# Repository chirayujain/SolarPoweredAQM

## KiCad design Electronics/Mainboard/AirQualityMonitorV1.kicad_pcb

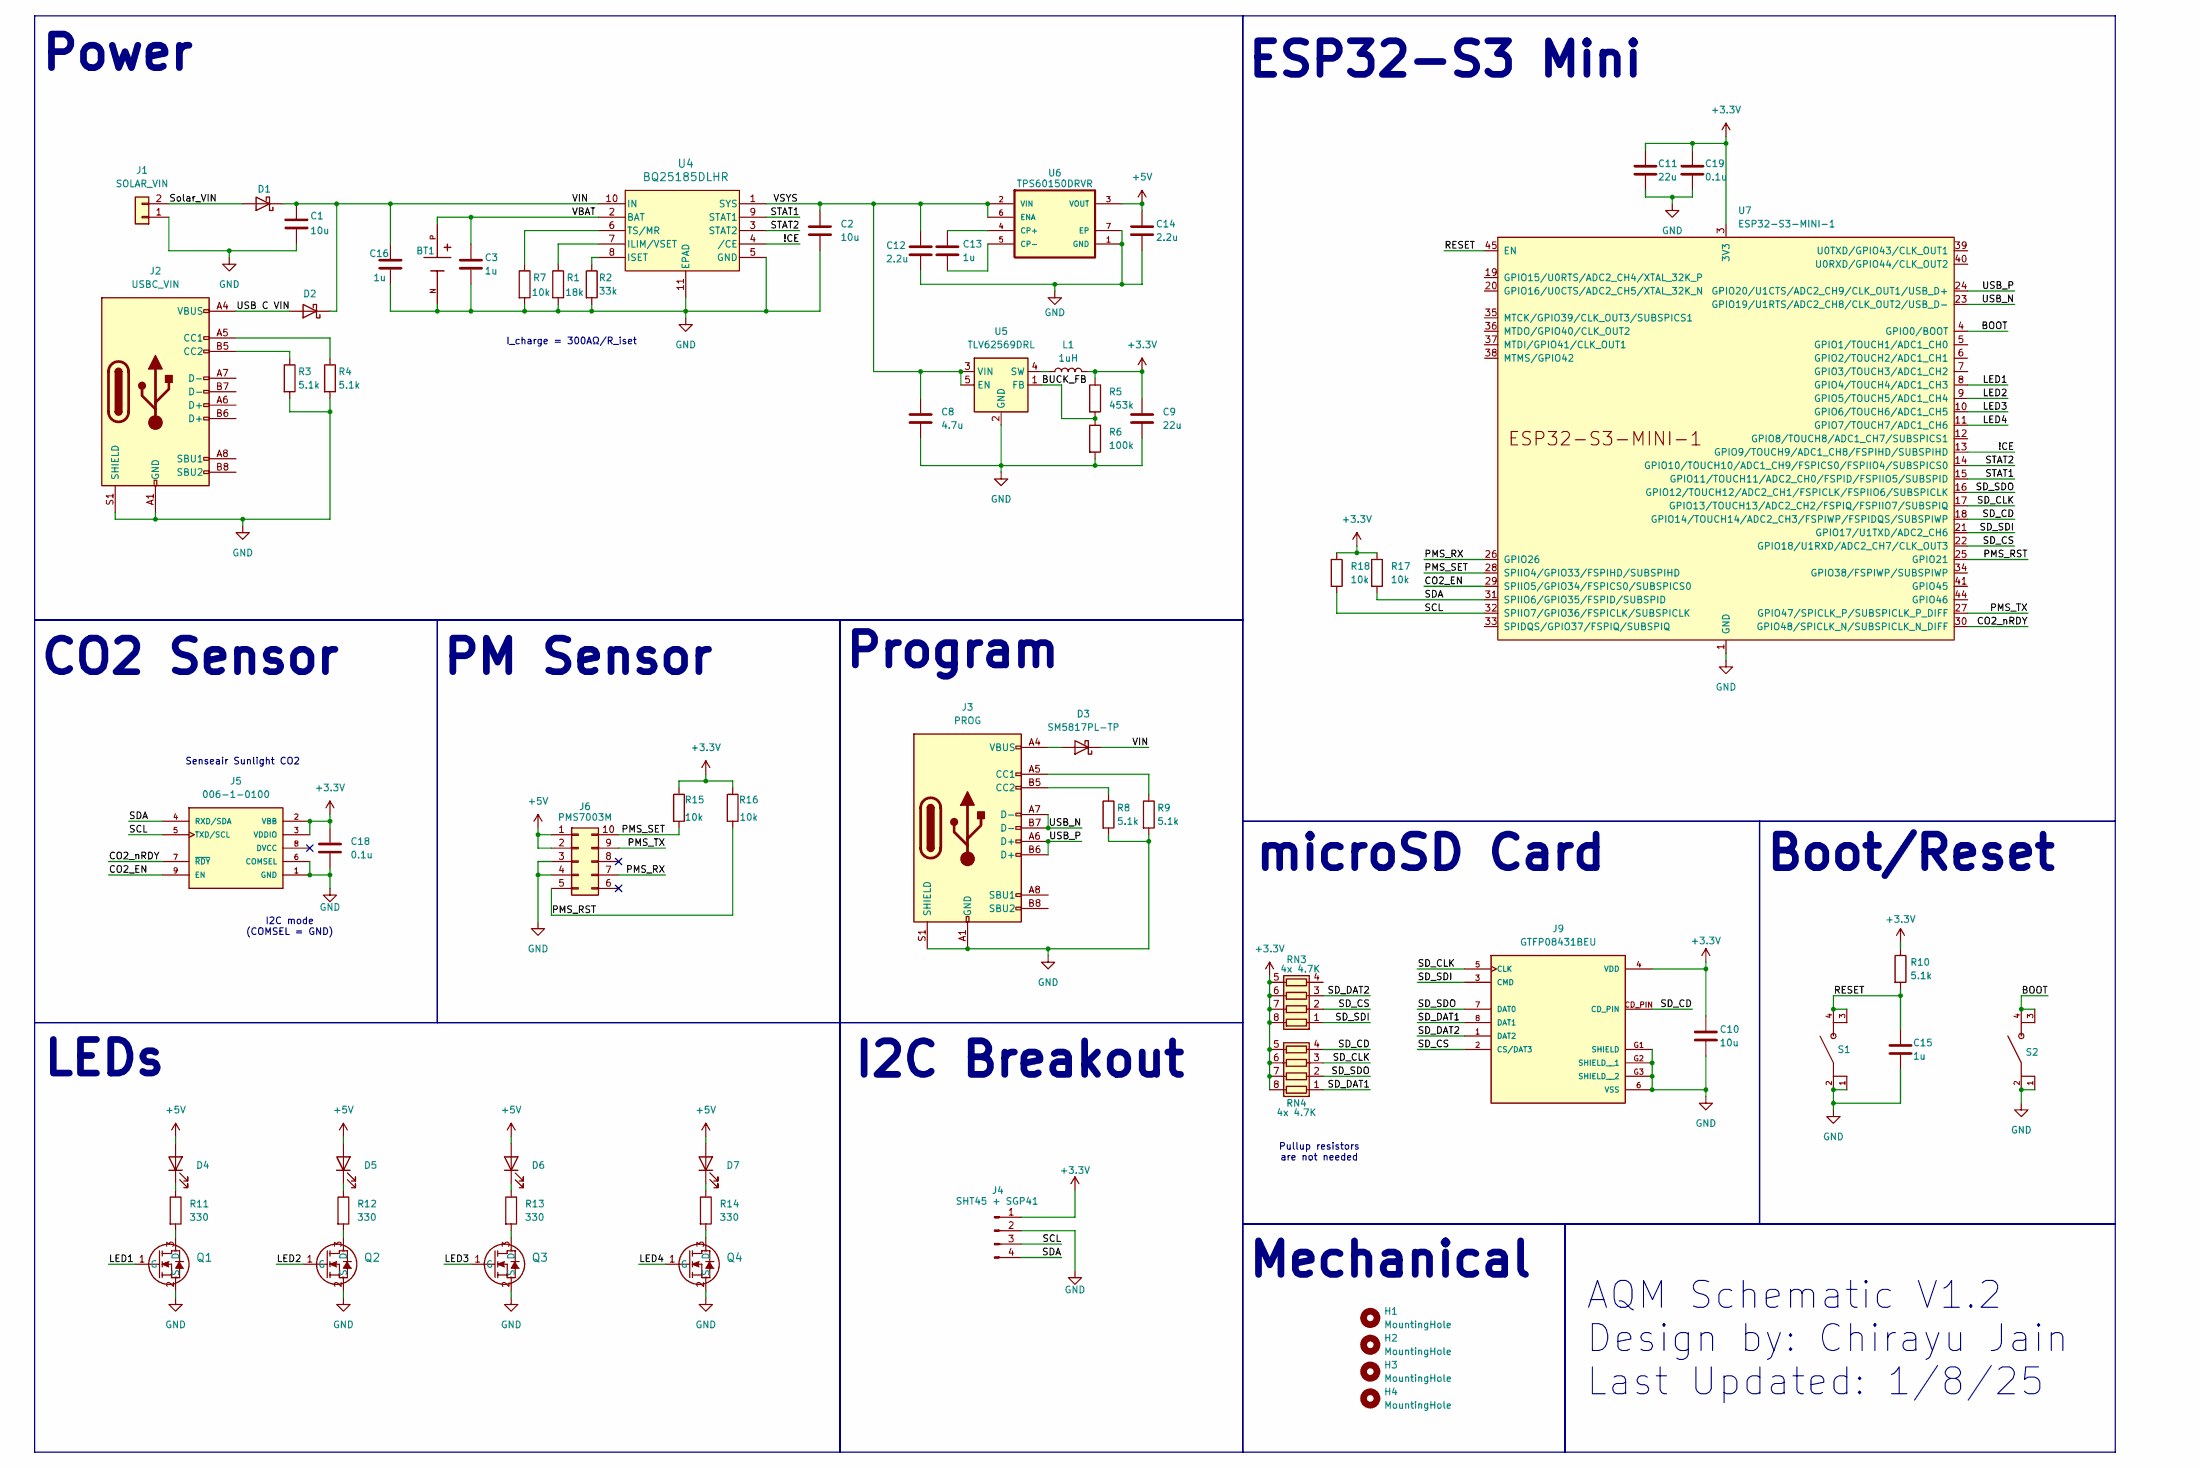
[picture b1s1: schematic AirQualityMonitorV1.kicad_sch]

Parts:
BT1: 1043; 1043_BAT_1043; PARTREV J
C1, C2, C10: 10u; C_0603_1608Metric
C3, C13, C15, C16: 1u; C_0603_1608Metric
C8: 4.7u; C_0603_1608Metric
C9, C11: 22u; C_0603_1608Metric
C12, C14: 2.2u; C_0603_1608Metric
C18, C19: 0.1u; C_0603_1608Metric
D1, D2, D3: SM5817PL-TP; D_SOD-123F
D4, D5, D6, D7: LED; LED_Luminus_MP-3030-1100_3.0x3.0mm
H1, H2, H3, H4: MountingHole; MountingHole_3.2mm_M3
J1: SOLAR_VIN; PinHeader_1x02_P2.54mm_Vertical
J2: USBC_VIN; USB_C_Receptacle_GCT_USB4105-xx-A_16P_TopMnt_Horizontal
J3: PROG; USB_C_Receptacle_GCT_USB4105-xx-A_16P_TopMnt_Horizontal
J4: SHT45 + SGP41; PinHeader_1x04_P2.54mm_Vertical
J5: 006-1-0100; 006-0-0002_XDCR_006-0-0002; PARTREV 1.00.000
J6: PMS7003M; PinSocket_2x05_P1.27mm_Vertical
J9: GTFP08431BEU; GTFP08431BEU_AMPHENOL_GTFP08431BEU; PARTREV F
L1: 1uH; L_Coilcraft_XxL4020
Q1, Q2, Q3, Q4: AO3422; SOT23_AOS
R1: 18k; R_0603_1608Metric
R2: 33k; R_0603_1608Metric
R3, R4, R8, R9, R10: 5.1k; R_0603_1608Metric
R5: 453k; R_0603_1608Metric
R6: 100k; R_0603_1608Metric
R7, R15, R16, R17, R18: 10k; R_0603_1608Metric
R11, R12, R13, R14: 330; R_0603_1608Metric
RN3, RN4: 4x 4.7K; R_Array_Convex_4x1206
S1, S2: PTS815_SJG
U4: BQ25185DLHR; WSON10_DLH_TEX
U5: TLV62569DRL; SOT-563
U6: TPS60150DRVR; TPS60150DRVR_SON65P200X200X80-7N
U7: ESP32-S3-MINI-1

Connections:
+3.3V: C9.1, C10.1, C11.1, C18.1, C19.1, J4.1, J5.2 (VBB), J5.3 (VDDIO), J9.4 (VDD), L1.2, R5.1, R10.1, R15.1, R16.1, R17.1, R18.1, RN3.5 (R4.2), RN3.6 (R3.2), RN3.7 (R2.2), RN3.8 (R1.2), RN4.5 (R4.2), RN4.6 (R3.2), RN4.7 (R2.2), RN4.8 (R1.2), U7.3 (3V3)
+5V: C14.1, D4.2 (A), D5.2 (A), D6.2 (A), D7.2 (A), J6.1, J6.2, U6.3 (VOUT)
/!CE: U4.4 (/CE), U7.13 (GPIO9/TOUCH9/ADC1_CH8/FSPIHD/SUBSPIHD)
/BOOT: S2.3, S2.4, U7.4 (GPIO0/BOOT)
/BUCK_FB: R5.2, R6.1, U5.1 (FB)
/CO2_EN: J5.9 (EN), U7.29 (SPIIO5/GPIO34/FSPICS0/SUBSPICS0)
/CO2_nRDY: J5.7 (~RDY), U7.30 (GPIO48/SPICLK_N/SUBSPICLK_N_DIFF)
/LED1: Q1.1 (G), U7.8 (GPIO4/TOUCH4/ADC1_CH3)
/LED2: Q2.1 (G), U7.9 (GPIO5/TOUCH5/ADC1_CH4)
/LED3: Q3.1 (G), U7.10 (GPIO6/TOUCH6/ADC1_CH5)
/LED4: Q4.1 (G), U7.11 (GPIO7/TOUCH7/ADC1_CH6)
/PMS_RST: J6.5, R16.2, U7.25 (GPIO21)
/PMS_RX: J6.7, U7.26 (GPIO26)
/PMS_SET: J6.10, R15.2, U7.28 (SPIIO4/GPIO33/FSPIHD/SUBSPIHD)
/PMS_TX: J6.9, U7.27 (GPIO47/SPICLK_P/SUBSPICLK_P_DIFF)
/RESET: C15.1, R10.2, S1.3, S1.4, U7.45 (EN)
/SCL: J4.3, J5.5 (TXD/SCL), R18.2, U7.32 (SPIIO7/GPIO36/FSPICLK/SUBSPICLK)
/SDA: J4.4, J5.4 (RXD/SDA), R17.2, U7.31 (SPIIO6/GPIO35/FSPID/SUBSPID)
/SD_CD: J9.CD_PIN, RN4.4 (R4.1), U7.18 (GPIO14/TOUCH14/ADC2_CH3/FSPIWP/FSPIDQS/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)
/SD_CLK: J9.5 (CLK), RN4.3 (R3.1), U7.17 (GPIO13/TOUCH13/ADC2_CH2/FSPIQ/FSPIIO7/S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)
/SD_CS: J9.2 (CS/DAT3), RN3.2 (R2.1), U7.22 (GPIO18/U1RXD/ADC2_CH7/CLK_OUT3)
/SD_DAT1: J9.8 (DAT1), RN4.1 (R1.1)
/SD_DAT2: J9.1 (DAT2), RN3.3 (R3.1)
/SD_SDI: J9.3 (CMD), RN3.1 (R1.1), U7.21 (GPIO17/U1TXD/ADC2_CH6)
/SD_SDO: J9.7 (DAT0), RN4.2 (R2.1), U7.16 (GPIO12/TOUCH12/ADC2_CH1/FSPICLK/FSPIIO6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)
/STAT1: U4.9 (STAT1), U7.15 (GPIO11/TOUCH11/ADC2_CH0/FSPID/FSPIIO5/S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)
/STAT2: U4.3 (STAT2), U7.14 (GPIO10/TOUCH10/ADC1_CH9/FSPICS0/FSPIIO4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)
/Solar_VIN: D1.2 (A), J1.2
/USB C VIN: D2.2 (A), J2.A4 (VBUS), J2.A9 (VBUS), J2.B4 (VBUS), J2.B9 (VBUS)
/USB_N: J3.A7 (D-), J3.B7 (D-), U7.23 (GPIO19/U1RTS/ADC2_CH8/CLK_OUT2/USB_D-)
/USB_P: J3.A6 (D+), J3.B6 (D+), U7.24 (GPIO20/U1CTS/ADC2_CH9/CLK_OUT1/USB_D+)
/VBAT: BT1.P, C3.1, U4.2 (BAT)
/VIN: C1.1, C16.1, D1.1 (K), D2.1 (K), D3.1 (K), U4.10 (IN)
/VSYS: C2.1, C8.1, C12.1, U4.1 (SYS), U5.3 (VIN), U5.5 (EN), U6.2 (VIN), U6.6 (ENA)
GND: BT1.N, C1.2, C2.2, C3.2, C8.2, C9.2, C10.2, C11.2, C12.2, C14.2, C15.2, C16.2, C18.2, C19.2, J1.1, J2.A1 (GND), J2.A12 (GND), J2.B1 (GND), J2.B12 (GND), J2.S1 (SHIELD), J3.A1 (GND), J3.A12 (GND), J3.B1 (GND), J3.B12 (GND), J3.S1 (SHIELD), J4.2, J5.1 (GND), J5.6 (COMSEL), J6.3, J6.4, J9.6 (VSS), J9.G1 (SHIELD), J9.G2 (SHIELD__1), J9.G3 (SHIELD__2), Q1.2 (S), Q2.2 (S), Q3.2 (S), Q4.2 (S), R1.2, R2.2, R3.2, R4.2, R6.2, R7.2, R8.2, R9.2, S1.1, S1.2, S2.1, S2.2, U4.5 (GND), U4.11 (EPAD), U5.2 (GND), U6.1 (GND), U6.7 (EP), U7.1 (GND), U7.2 (GND), U7.42 (GND), U7.43 (GND), U7.46 (GND), U7.47 (GND), U7.48 (GND), U7.49 (GND), U7.50 (GND), U7.51 (GND), U7.52 (GND), U7.53 (GND), U7.54 (GND), U7.55 (GND), U7.56 (GND), U7.57 (GND), U7.58 (GND), U7.59 (GND), U7.60 (GND), U7.61 (GND), U7.62 (GND), U7.63 (GND), U7.64 (GND), U7.65 (GND)
unnamed: D3.2 (A), J3.A4 (VBUS), J3.A9 (VBUS), J3.B4 (VBUS), J3.B9 (VBUS)
unnamed: D4.1 (K), R11.1
unnamed: D5.1 (K), R12.1
unnamed: D6.1 (K), R13.1
unnamed: D7.1 (K), R14.1
unnamed: J2.A5 (CC1), R4.1
unnamed: J2.B5 (CC2), R3.1
unnamed: J3.A5 (CC1), R9.1
unnamed: J3.B5 (CC2), R8.1
unnamed: Q1.3 (D), R11.2
unnamed: Q2.3 (D), R12.2
unnamed: Q3.3 (D), R13.2
unnamed: Q4.3 (D), R14.2
unnamed: R1.1, U4.7 (ILIM/VSET)
unnamed: R2.1, U4.8 (ISET)
unnamed: R7.1, U4.6 (TS/MR)
unnamed: L1.1, U5.4 (SW)
unnamed: C13.1, U6.4 (CP+)
unnamed: C13.2, U6.5 (CP-)

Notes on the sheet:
AQM Schematic V1.2 Design by: Chirayu Jain Last Updated: 1/8/25
microSD Card
CO2 Sensor
Senseair Sunlight CO2
ESP32-S3 Mini
Power
LEDs
PM Sensor
I2C Breakout
Mechanical
Boot/Reset
Pullup resistors are not needed
I_charge = 300AΩ/R_iset
I2C mode (COMSEL = GND)
Program

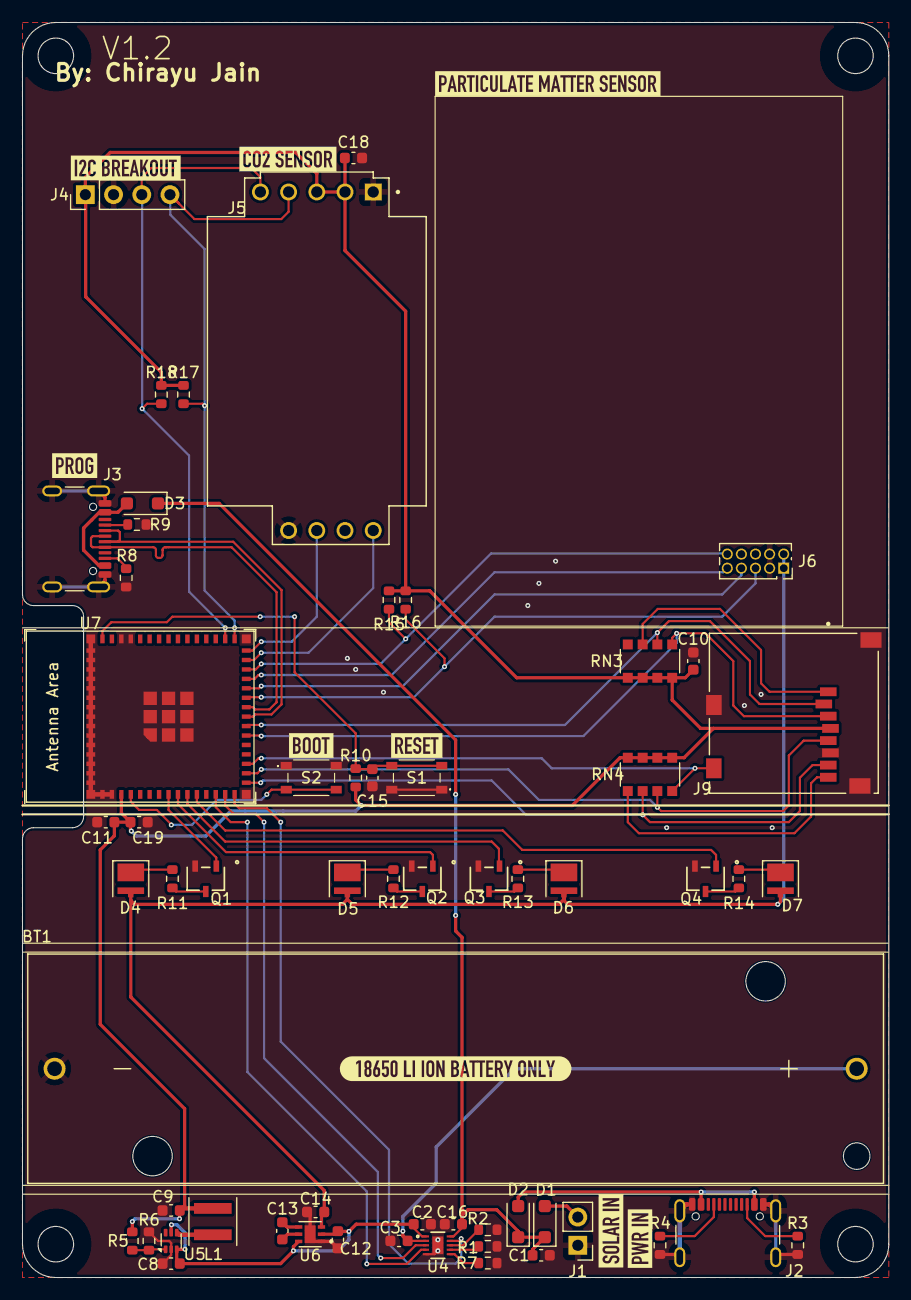
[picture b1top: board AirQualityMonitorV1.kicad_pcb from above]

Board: 2 copper layers, 78.0 x 113.0 mm, 73 parts (0 on the bottom side), 54 nets.

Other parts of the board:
kibuzzard-66CA2A9F: G***; kibuzzard-66CA2A9F
kibuzzard-66CA2A40: G***; kibuzzard-66CA2A40
kibuzzard-66CA2A73: G***; kibuzzard-66CA2A73
kibuzzard-66CA2ABD: G***; kibuzzard-66CA2ABD
kibuzzard-66CA2AE0: G***; kibuzzard-66CA2AE0
kibuzzard-66CA2B1F: G***; kibuzzard-66CA2B1F
kibuzzard-66CA2B19: G***; kibuzzard-66CA2B19
kibuzzard-66CA2899: G***; kibuzzard-66CA2899
kibuzzard-66CB4D05: G***; kibuzzard-66CB4D05

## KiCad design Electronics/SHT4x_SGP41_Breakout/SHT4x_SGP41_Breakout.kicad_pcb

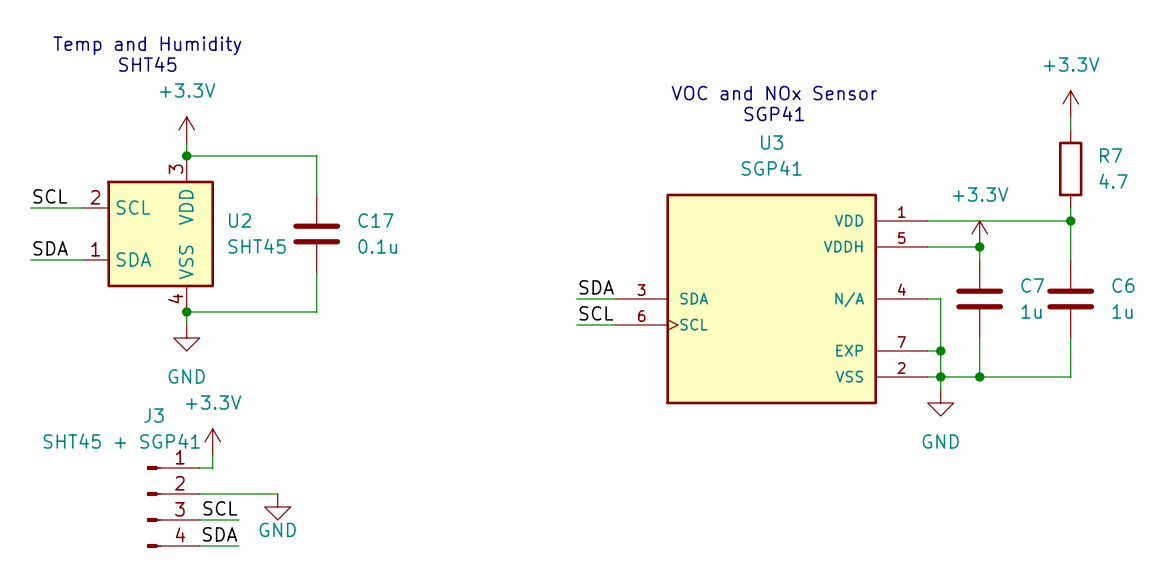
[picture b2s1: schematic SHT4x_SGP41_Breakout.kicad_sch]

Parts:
C6, C7: 1u; C_0603_1608Metric
C17: 0.1u; C_0603_1608Metric
J3: SHT45 + SGP41; PinHeader_1x04_P2.54mm_Vertical
R7: 4.7; R_0603_1608Metric
U2: SHT45; Sensirion_DFN-4_1.5x1.5mm_P0.8mm_SHT4x_NoCentralPad
U3: SGP41; SGP41-D-R4_XDCR_SGP41-D-R4; PARTREV 1.0

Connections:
+3.3V: C7.1, C17.1, J3.1, R7.1, U2.3 (VDD), U3.5 (VDDH)
/SCL: J3.3, U2.2 (SCL), U3.6 (SCL)
/SDA: J3.4, U2.1 (SDA), U3.3 (SDA)
GND: C6.2, C7.2, C17.2, J3.2, U2.4 (VSS), U3.2 (VSS), U3.4 (N/A), U3.7 (EXP)
unnamed: C6.1, R7.2, U3.1 (VDD)

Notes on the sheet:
Temp and Humidity SHT45
VOC and NOx Sensor SGP41

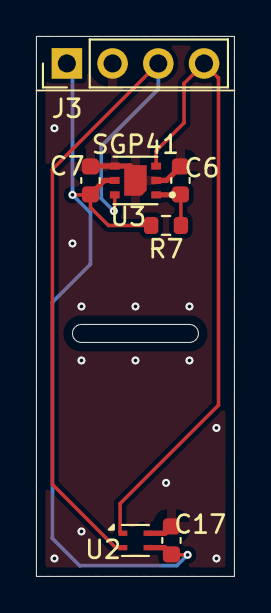
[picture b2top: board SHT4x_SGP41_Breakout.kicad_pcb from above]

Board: 2 copper layers, 11.0 x 30.0 mm, 7 parts (0 on the bottom side), 5 nets.

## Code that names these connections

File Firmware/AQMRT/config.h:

#ifndef CONFIG_H
#define CONFIG_H

// I2C Pins
#define SDA 35
#define SCL 36

// SPI Pins
#define SD_CS 18
#define SD_MOSI 17
#define SD_MISO 12
#define SD_SCK 13

// BMS Pins
#define STAT1 11
#define STAT2 10
#define CE 9

// LED Pins
#define LED1 4
#define LED2 5
#define LED3 6
#define LED4 7
#define LEDC_RES 8
#define LEDC_FREQ 20000

// PM2.5 Sensor Pins
#define PMS_RST 21
#define PMS_SET 33
#define PMS_TX 26
#define PMS_RX 47

// CO2 Sensor
#define CO2_EN 34
#define CO2_nRDY 48
#define CO2_ADDR 0x68




struct SensorData {
  struct tm timeinfo;
  bool stat1;
  bool stat2;
  float temperature;
  float rh;
  uint16_t voc_raw;
  uint16_t nox_raw;
  int32_t voc_index;
  int32_t nox_index;
  uint16_t co2_ppm;
  uint16_t pm1_0;
  uint16_t pm2_5;
  uint16_t pm10_0;
};



#endif

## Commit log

2025-01-18 Source Upload
2025-01-18 Create LICENSE
